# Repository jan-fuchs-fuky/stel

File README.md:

# Perek 2-m telescope SW

## C: CCD control

https://github.com/jan-fuchs-fuky/stel/blob/main/peso/src/exposed.c

https://github.com/jan-fuchs-fuky/stel/blob/main/peso/src/mod_ccd_bilbo.c

https://github.com/jan-fuchs-fuky/stel/blob/main/peso/src/mod_ccd_frodo.c

https://github.com/jan-fuchs-fuky/stel/blob/main/peso/src/mod_ccd_gandalf.c

https://github.com/jan-fuchs-fuky/stel/blob/main/peso/src/mod_ccd_sauron.c

## C: Spectrograph control

https://github.com/jan-fuchs-fuky/stel/blob/main/observe/src/spectrographd/spectrographd.c

## C: Telescope control

https://github.com/jan-fuchs-fuky/stel/blob/main/observe/src/telescoped/telescoped.c

## Java: Observe server and GUI

https://github.com/jan-fuchs-fuky/stel/tree/main/observe/src/cz/cas/asu/stelweb/fuky/observe

## Python: Toptec server and GUI

https://github.com/jan-fuchs-fuky/stel/blob/main/observe/service/bin/fiber_control_server.py

https://github.com/jan-fuchs-fuky/stel/blob/main/observe/service/systemd/fiber_control_server.service

https://github.com/jan-fuchs-fuky/stel/blob/main/observe/service/bin/fiber_control_client.py

## Python: Moravian Instruments camera control

https://github.com/jan-fuchs-fuky/stel/blob/main/observe/service/bin/fiber_gxccd_server.py

https://github.com/jan-fuchs-fuky/stel/blob/main/observe/service/systemd/fiber_gxccd_server_photometric.service

https://github.com/jan-fuchs-fuky/stel/blob/main/observe/service/systemd/fiber_gxccd_server_pointing.service

## Python: Observe Batch

https://github.com/jan-fuchs-fuky/stel/blob/main/observe/service/bin/observe_client.py

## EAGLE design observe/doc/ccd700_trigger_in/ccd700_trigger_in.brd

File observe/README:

http://tomcat.apache.org/tomcat-6.0-doc/logging.html

+-----------------------+
| Observe client - Java |
+-----------------------+
^
| Secure TCP/IP connections with SSL
v
+-------------------------+
| Observe server - Python |
+-------------------------+
^   ^   ^   ^   ^
|   |   |   |   | only one TCP/IP connection
|   |   |   |   v
|   |   |   |   +--------------------------------+
|   |   |   |   | Telescope server - ProjectSoft |
|   |   |   |   +--------------------------------+
|   |   |   |
|   |   |   | TCP/IP connections
|   |   |   v
|   |   |   +----------------------+
|   |   |   | OPSO server - Python |
|   |   |   +----------------------+
|   |   |
|   |   | TCP/IP connections
|   |   v
|   |   +-------------------+
|   |   | CCD400 server - C |
|   |   +-------------------+
|   |
|   | TCP/IP connections
|   v
|   +-------------------+
|   | CCD700 server - C |
|   +-------------------+
|
| TCP/IP connections
v
+----------------+
| OES server - C |
+----------------+

liblog4c-dev - http://log4c.sourceforge.net/
libxmlrpc-c3-dev - http://xmlrpc-c.sourceforge.net/

$ echo -n "heslo:salt" |sha512sum

$ DERBY_HOME=~/java/_derby/db-derby-10.4.1.3-bin ~/java/_derby/db-derby-10.4.1.3-bin/bin/ij
> CONNECT 'jdbc:derby:observeDB;';
> run 'sql/insert_admin.sql';

$ xmlrpc http://primula:9999/RPC2 telescope_info
Result:

Struct of 8 members:
  Key:   String: 'glst'
  Value: String: '0 1 0 0 0 1 4 4 4 511 0 0 0 0'
  Key:   String: 'trrd'
  Value: String: '143716.800 +800119.80 0'
  Key:   String: 'trhd'
  Value: String: '9.9946 80.0065'
  Key:   String: 'trgv'
  Value: String: '-0.2 -6.3'
  Key:   String: 'trus'
  Value: String: '0.0000 0.0000'
  Key:   String: 'dopo'
  Value: String: '49.63'
  Key:   String: 'trcs'
  Value: String: '0'
  Key:   String: 'fopo'
  Value: String: '18.85'

# vim /etc/apt/sources.list
deb http://ftp.cz.debian.org/debian/ experimental main non-free contrib
# aptitude update && aptitude install libxmlrpc-c3-dev=1.16.07-1

# OBSERVED_DIR=$PWD ./init.d/observed start

*** Tomcat ***

http://tomcat.apache.org/migration-7.html
http://tomcat.apache.org/migration-8.html
http://tomcat.apache.org/migration-85.html

# vim /etc/default/tomcat6
JAVA_HOME=/usr/lib/jvm/java-6-sun

# rsync -a class /var/lib/tomcat6/webapps/observe/WEB-INF/classes
# rsync -a lib /var/lib/tomcat6/webapps/observe/WEB-INF/lib

# vim /var/lib/tomcat6/webapps/observe/WEB-INF/web.xml 
<?xml version="1.0" encoding="UTF-8"?>
<web-app xmlns:xsi="http://www.w3.org/2001/XMLSchema-instance" xmlns="http://java.sun.com/xml/ns/javaee" xmlns:web="http://java.sun.com/xml/ns/javaee/web-app_2_5.xsd" xsi:schemaLocation="http://java.sun.com/xml/ns/javaee http://java.sun.com/xml/ns/javaee/web-app_2_5.xsd" id="WebApp_ID" version="2.5">
    <display-name>Observe</display-name>
    <servlet>
        <servlet-name>Jersey REST Service</servlet-name>
        <servlet-class>com.sun.jersey.spi.container.servlet.ServletContainer</servlet-class>

        <init-param>
          <param-name>com.sun.jersey.config.property.packages</param-name>
          <param-value>cz.cas.asu.stelweb.fuky.observe.resources;cz.cas.asu.stelweb.fuky.observe.auth</param-value>
        </init-param>

        <init-param> 
          <param-name>com.sun.jersey.spi.container.ContainerRequestFilters</param-name> 
          <param-value>cz.cas.asu.stelweb.fuky.observe.auth.SecurityFilter</param-value> 
        </init-param>

        <init-param> 
          <param-name>com.sun.jersey.spi.container.filter.ResourceFilterFactory</param-name> 
          <param-value>com.sun.jersey.api.container.filter.RolesAllowedResourceFilterFactory</param-value> 
        </init-param>

<!--
        <init-param> 
          <param-name>com.sun.jersey.config.property.resourceConfigClass</param-name> 
          <param-value>com.sun.jersey.api.core.PackagesResourceConfig</param-value> 
        </init-param>
-->

        <load-on-startup>1</load-on-startup>
    </servlet>
    <servlet-mapping>
        <servlet-name>Jersey REST Service</servlet-name>
        <url-pattern>/observe/*</url-pattern>
    </servlet-mapping>
</web-app>

# chown -R tomcat6.tomcat6 /var/lib/tomcat6/webapps/observe

# vim /etc/tomcat6/Catalina/localhost/observe.xml
<Context path="/observe" 
	docBase="/var/lib/tomcat6/webapps/observe" />

# /etc/init.d/tomcat6 restart

http://tomcat.apache.org/tomcat-6.0-doc/realm-howto.html
http://www.mysql.com/downloads

mysql-connector-java-5.1.17.zip

Nainstalovat:

    # aptitude install libmysql-java

nebo:

    # cp mysql-connector-java-5.1.17-bin.jar /usr/share/java

# cd /usr/share/tomcat6/lib/
# ln -s ../../java/mysql-connector-java-5.1.17-bin.jar .

# vim /etc/tomcat6/server.xml
    <Realm className="org.apache.catalina.realm.JDBCRealm"
         digest="MD5"
         driverName="com.mysql.jdbc.Driver"
         connectionURL="jdbc:mysql://localhost:3306/observe?user=root&amp;password=heslo"
         userTable="users" userNameCol="user_name" userCredCol="user_pass"
         userRoleTable="user_roles" roleNameCol="role_name" />

    <Connector port="8443" protocol="HTTP/1.1" SSLEnabled="true"
               maxThreads="150" scheme="https" secure="true"
               clientAuth="false" sslProtocol="TLS" />

create table users (
  user_name         varchar(15) not null primary key,
  user_pass         varchar(15) not null
);

create table user_roles (
  user_name         varchar(15) not null,
  role_name         varchar(15) not null,
  primary key (user_name, role_name)
);

# cd /usr/share/tomcat6/
# keytool -genkey -alias tomcat -keyalg RSA -keystore .keystore

specify a password value of "changeit"

Debug log:

    # vim /etc/tomcat6/logging.properties
    org.apache.catalina.level=ALL

Access log:

    # vim /etc/tomcat6/server.xml
    <Valve className="org.apache.catalina.valves.AccessLogValve" directory="logs"  
           prefix="localhost_access_log." suffix=".txt" pattern="common" resolveHosts="false"/>

SEVERE: Failed to initialize connector [Connector[HTTP/1.1-443]]
LifecycleException:  Protocol handler initialization failed: java.io.FileNotFoundException: /usr/share/tomcat6/.keystore (No such file or directory)

    Tomcat 6: Binding to a Privileged Port on Debian/Ubuntu:
    http://thelowedown.wordpress.com/2010/08/17/tomcat-6-binding-to-a-privileged-port-on-debianubuntu/

    # vim /etc/default/tomcat6
    AUTHBIND=yes

*** Errors ***

http://stackoverflow.com/questions/30119664/how-to-configure-tomcat-7-with-ssl-on-ubuntu-14-the-unanswered-questions

    To address this part of the above problem reported in catalina.out...
    
    SEVERE: Failed to initialize end point associated with ProtocolHandler ["http-bio-443"]
    java.net.SocketException: No such file or directory

    For me this was caused by tomcat not being allowed to bind to port 443, and
    was nothing to do with the keystore/certificates.
    
    I fixed it by running...
    
        # touch /etc/authbind/byport/443 
        # chmod 500 /etc/authbind/byport/443 
        # chown tomcat7 /etc/authbind/byport/443

    if you don't have authbind installed, install it via
    
        # apt-get install authbind

Caused by:
com.mysql.jdbc.exceptions.jdbc4.MySQLNonTransientConnectionException: Data
source rejected establishment of connection,  message from server: "Too many
connections"

http://www.coderanch.com/t/497782/ORM/java/Too-many-connections

    I had solved the problem by using "mysql.allow_persistent=Off" in configuration file to persist data
    and it's closed connection wheather connection is opened.
    
    Another way to use "set-variable=max_connections=250" this syntax in same configuration file to
    manage maximum connection.

http://www.devdaily.com/blog/post/mysql/how-show-open-database-connections-mysql

    mysql> show status like 'Conn%';
    +---------------+-------+
    | Variable_name | Value |
    +---------------+-------+
    | Connections   | 273   | 
    +---------------+-------+
    1 row in set (0.00 sec)

    mysql> show status like '%onn%';
    +--------------------------+-------+
    | Variable_name            | Value |
    +--------------------------+-------+
    | Aborted_connects         | 15    | 
    | Connections              | 273   | 
    | Max_used_connections     | 101   | 
    | Ssl_client_connects      | 0     | 
    | Ssl_connect_renegotiates | 0     | 
    | Ssl_finished_connects    | 0     | 
    | Threads_connected        | 25    | 
    +--------------------------+-------+
    7 rows in set (0.00 sec)

    mysql> show processlist;
    +-----+------+-----------------+---------+---------+------+-------+------------------+
    | Id  | User | Host            | db      | Command | Time | State | Info             |
    +-----+------+-----------------+---------+---------+------+-------+------------------+
    | 248 | root | localhost:34364 | observe | Sleep   |   27 |       | NULL             | 
    | 249 | root | localhost:34365 | observe | Sleep   | 1903 |       | NULL             | 
    | 250 | root | localhost:34374 | observe | Sleep   | 1886 |       | NULL             | 
    | 251 | root | localhost:34397 | observe | Sleep   | 1827 |       | NULL             | 
    | 252 | root | localhost:34421 | observe | Sleep   | 1767 |       | NULL             | 
    | 253 | root | localhost:34445 | observe | Sleep   | 1707 |       | NULL             | 
    | 254 | root | localhost:45794 | observe | Sleep   | 1646 |       | NULL             | 
    | 255 | root | localhost:45818 | observe | Sleep   | 1586 |       | NULL             | 
    | 256 | root | localhost:45841 | observe | Sleep   | 1527 |       | NULL             | 
    | 257 | root | localhost:45866 | observe | Sleep   | 1467 |       | NULL             | 
    | 258 | root | localhost:45889 | observe | Sleep   | 1407 |       | NULL             | 
    | 259 | root | localhost:40382 | observe | Sleep   | 1347 |       | NULL             | 
    | 260 | root | localhost:40406 | observe | Sleep   | 1286 |       | NULL             | 
    | 261 | root | localhost:40430 | observe | Sleep   | 1227 |       | NULL             | 
    | 262 | root | localhost:40454 | observe | Sleep   | 1167 |       | NULL             | 
    | 263 | root | localhost:40476 | observe | Sleep   | 1107 |       | NULL             | 
    | 264 | root | localhost:42970 | observe | Sleep   | 1046 |       | NULL             | 
    | 265 | root | localhost:42995 | observe | Sleep   |  987 |       | NULL             | 
    | 266 | root | localhost:43019 | observe | Sleep   |  927 |       | NULL             | 
    | 267 | root | localhost:43042 | observe | Sleep   |  867 |       | NULL             | 
    | 268 | root | localhost:43067 | observe | Sleep   |  807 |       | NULL             | 
    | 269 | root | localhost:35916 | observe | Sleep   |  746 |       | NULL             | 
    | 270 | root | localhost:35917 | observe | Sleep   |  746 |       | NULL             | 
    | 271 | root | localhost:49434 | observe | Sleep   |  346 |       | NULL             | 
    | 272 | root | localhost       | NULL    | Query   |    0 | NULL  | show processlist | 
    +-----+------+-----------------+---------+---------+------+-------+------------------+
    25 rows in set (0.01 sec)

    # mysqladmin status
    Uptime: 96592  Threads: 25  Questions: 15495  Slow queries: 0  Opens: 152
    Flush tables: 2  Open tables: 19  Queries per second avg: 0.160

Caused by: com.mysql.jdbc.exceptions.jdbc4.CommunicationsException: The last
packet successfully received from the server was 52 421 389 milliseconds ago.
The last packet sent successfully to the server was 52 421 389 milliseconds
ago. is longer than the server configured value of 'wait_timeout'. You should
consider either expiring and/or testing connection validity before use in your
application, increasing the server configured values for client timeouts, or
using the Connector/J connection property 'autoReconnect=true' to avoid this
problem.

    http://codingclues.eu/2009/commysqljdbcexceptionsjdbc4communicationsexception/

    <property name="connection.autoReconnect">true</property>
    <property name="connection.autoReconnectForPools">true</property>
    <property name="connection.is-connection-validation-required">true</property>

    <property name="hibernate.c3p0.min_size" value="3" />
    <property name="hibernate.c3p0.max_size" value="50" />
    <property name="hibernate.c3p0.timeout" value="1800" />
    <property name="hibernate.c3p0.max_statements" value="50" />
    <!–- this property forces the revalidation of a connection after the given amount of time (in secs) –->
    <!–- it must be set to LESS than the wait_timout setting for the mysql server (this setting defaults to 28800 secs (8 hours)) –->
    <property name="hibernate.c3p0.idle_test_period" value="28680" />

    See manual http://dev.mysql.com/doc/mysql/en/show-variables.html
    'SHOW VARIABLES LIKE' returns value of the session variables.
    To return value of global variable you can use 'show global variables'.

    mysql> SHOW VARIABLES LIKE 'wait_%'; 
    +---------------+-------+
    | Variable_name | Value |
    +---------------+-------+
    | wait_timeout  | 28800 | 
    +---------------+-------+
    1 row in set (0.00 sec)

    mysql> SELECT @@GLOBAL.wait_timeout;
    +-----------------------+
    | @@GLOBAL.wait_timeout |
    +-----------------------+
    |                 28800 | 
    +-----------------------+
    1 row in set (0.00 sec)

    mysql> SET GLOBAL wait_timeout=30;
    Query OK, 0 rows affected (0.00 sec)

AstroPCI:

    ERROR 0x544F5554 = TOUT   A timeout has occurred. The destination board has failed to respond.

*** dependencies ***

$ ant jdeps -Djdeps.option="-R -s" |grep exec |cut -f9 -d " " |sort |uniq
./class
not

/opt/jdk1.8.0_40/jre/lib/jce.jar
/opt/jdk1.8.0_40/jre/lib/rt.jar

libantlr-java                 - /var/fasthome/fuky/git/observe/lib/java/antlr-2.7.6.jar
libasm3-java                  - /var/fasthome/fuky/git/observe/lib/java/asm-3.1.jar
libcommons-codec-java         - /var/fasthome/fuky/git/observe/lib/java/commons-codec-1.4.jar
libcommons-collections3-java  - /var/fasthome/fuky/git/observe/lib/java/commons-collections-3.1.jar
libdom4j-java                 - /var/fasthome/fuky/git/observe/lib/java/dom4j-1.6.1.jar
libfreemarker-java            - /var/fasthome/fuky/git/observe/lib/java/freemarker.jar
libhibernate3-java            - /var/fasthome/fuky/git/observe/lib/java/hibernate3.jar
libjavassist-java             - /var/fasthome/fuky/git/observe/lib/java/javassist-3.12.0.GA.jar
libjsr311-api-java            - /var/fasthome/fuky/git/observe/lib/java/jsr311-api-1.1.jar
jta                           - /var/fasthome/fuky/git/observe/lib/java/jta-1.1.jar
junit4                        - /var/fasthome/fuky/git/observe/lib/java/junit-4.11-SNAPSHOT-20120416-1530.jar
libmail-java                  - /var/fasthome/fuky/git/observe/lib/java/mail.jar
libslf4j-java                 - /var/fasthome/fuky/git/observe/lib/java/slf4j-api-1.7.2.jar
libslf4j-java                 - /var/fasthome/fuky/git/observe/lib/java/slf4j-nop-1.7.2.jar
libws-commons-util-java       - /var/fasthome/fuky/git/observe/lib/java/ws-commons-util-1.0.2.jar
libxmlrpc3-client-java        - /var/fasthome/fuky/git/observe/lib/java/xmlrpc-client-3.1.3.jar
libxmlrpc3-common-java        - /var/fasthome/fuky/git/observe/lib/java/xmlrpc-common-3.1.3.jar

NOT FOUND                     - /var/fasthome/fuky/git/observe/lib/java/jersey-client-1.3.jar
NOT FOUND                     - /var/fasthome/fuky/git/observe/lib/java/jersey-core-1.3.jar
NOT FOUND                     - /var/fasthome/fuky/git/observe/lib/java/jersey-server-1.3.jar
NOT FOUND                     - /var/fasthome/fuky/git/observe/lib/java/grizzly-servlet-webserver-1.9.18-i.jar
NOT FOUND                     - /var/fasthome/fuky/git/observe/lib/java/hibernate-jpa-2.0-api-1.0.1.Final.jar
NOT FOUND                     - /var/fasthome/fuky/git/observe/lib/java/jsky-coords.jar
NOT FOUND                     - /var/fasthome/fuky/git/observe/lib/java/jsky-elevation-plot.jar
NOT FOUND                     - /var/fasthome/fuky/git/observe/lib/java/jsky-util.jar

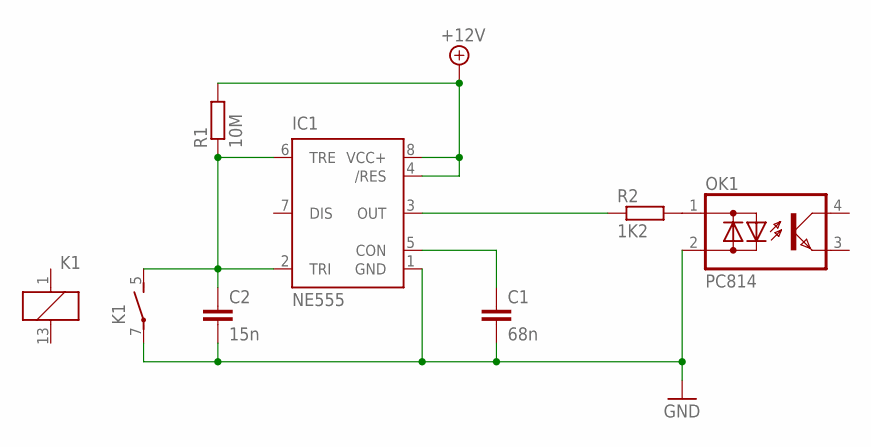
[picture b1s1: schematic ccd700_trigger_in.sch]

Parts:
C1: 68n; C5B3
C2: 15n; C5B3
IC1: NE555; DIL-08
K1: G6D-1A-ASI5VDC; G6D
OK1: PC814; DIL04
R1: 10M; 0204/7
R2: 1K2; 0204/7

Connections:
+12V: IC1.4 (/RES), IC1.8 (VCC+), R1.2
GND: C1.2, C2.2, IC1.1 (GND), K1.7, OK1.2 (AC2)
unnamed: C1.1, IC1.5 (CON)
unnamed: IC1.3 (OUT), R2.1
unnamed: C2.1, IC1.2 (TRI), IC1.6 (TRE), K1.5 (S), R1.1
unnamed: OK1.1 (AC1), R2.2

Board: 2 copper layers, 7 parts (0 on the bottom side), 6 nets, no tracks yet.

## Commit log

2024-01-10 Inital commit.
2024-01-10 README.md
